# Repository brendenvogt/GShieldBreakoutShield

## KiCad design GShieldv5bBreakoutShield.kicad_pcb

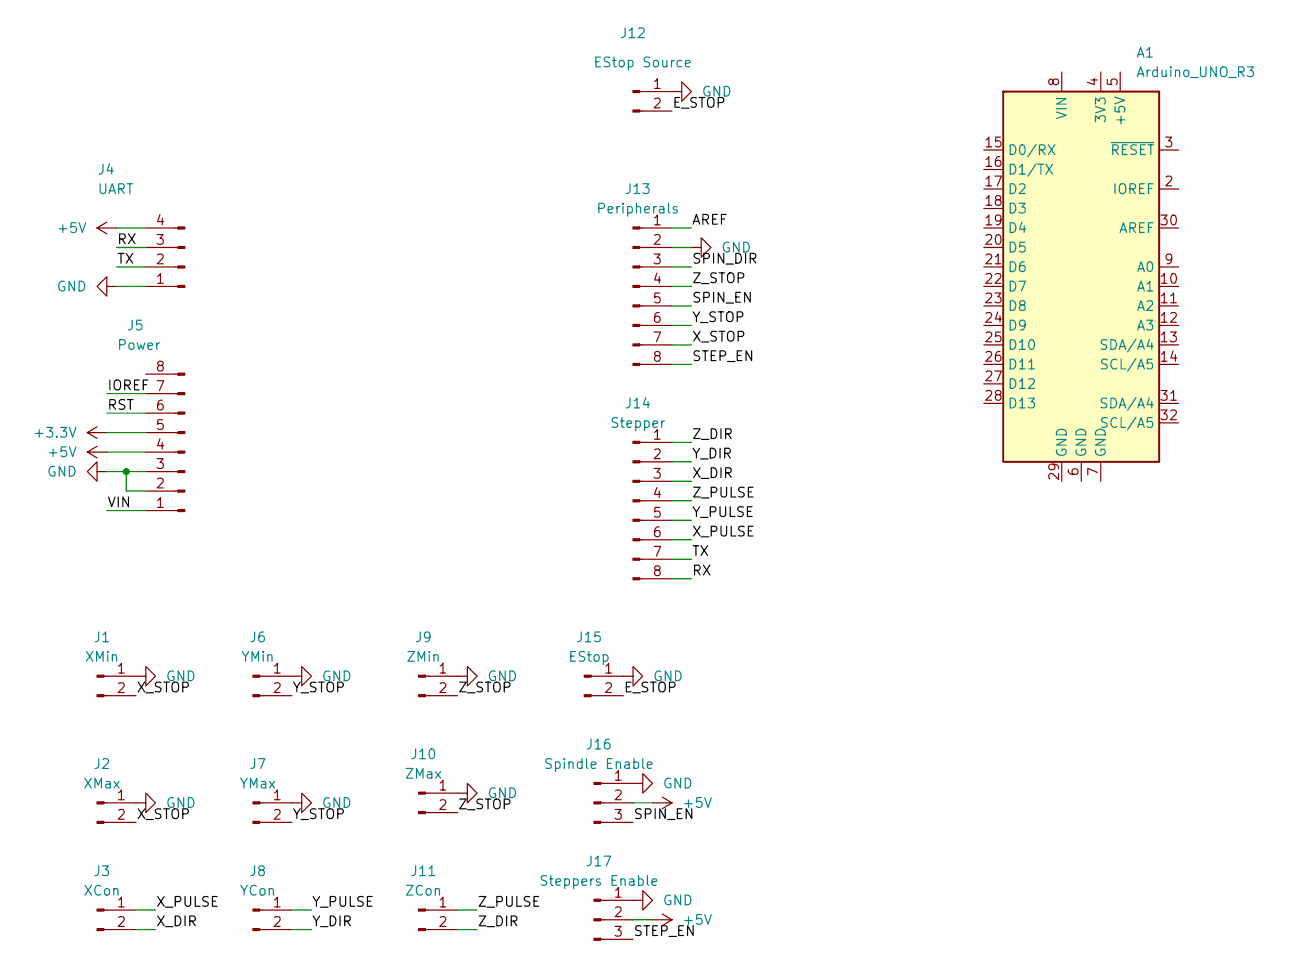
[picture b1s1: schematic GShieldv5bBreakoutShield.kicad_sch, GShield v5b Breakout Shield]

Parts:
A1: Arduino_UNO_R3
J1: XMin; PinHeader_1x02_P2.54mm_Vertical
J2: XMax; PinHeader_1x02_P2.54mm_Vertical
J3: XCon; PinHeader_1x02_P2.54mm_Vertical
J4: UART; PinHeader_1x04_P2.54mm_Vertical
J5: Power; PinHeader_1x08_P2.54mm_Vertical
J6: YMin; PinHeader_1x02_P2.54mm_Vertical
J7: YMax; PinHeader_1x02_P2.54mm_Vertical
J8: YCon; PinHeader_1x02_P2.54mm_Vertical
J9: ZMin; PinHeader_1x02_P2.54mm_Vertical
J10: ZMax; PinHeader_1x02_P2.54mm_Vertical
J11: ZCon; PinHeader_1x02_P2.54mm_Vertical
J12: EStop Source; PinHeader_1x02_P2.54mm_Vertical
J13: Peripherals; PinHeader_1x08_P2.54mm_Vertical
J14: Stepper; PinHeader_1x08_P2.54mm_Vertical
J15: EStop; PinHeader_1x02_P2.54mm_Vertical
J16: Spindle Enable; PinHeader_1x03_P2.54mm_Vertical
J17: Steppers Enable; PinHeader_1x03_P2.54mm_Vertical

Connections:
+3V3: J5.5
+5V: J4.4, J5.4, J16.2, J17.2
/AREF: J13.1
/E_STOP: J12.2, J15.2
/IOREF: J5.7
/RST: J5.6
/RX: J4.3, J14.8
/SPIN_DIR: J13.3
/SPIN_EN: J13.5, J16.3
/STEP_EN: J13.8, J17.3
/TX: J4.2, J14.7
/VIN: J5.1
/X_DIR: J3.2, J14.3
/X_PULSE: J3.1, J14.6
/X_STOP: J1.2, J2.2, J13.7
/Y_DIR: J8.2, J14.2
/Y_PULSE: J8.1, J14.5
/Y_STOP: J6.2, J7.2, J13.6
/Z_DIR: J11.2, J14.1
/Z_PULSE: J11.1, J14.4
/Z_STOP: J9.2, J10.2, J13.4
GND: J1.1, J2.1, J4.1, J5.2, J5.3, J6.1, J7.1, J9.1, J10.1, J12.1, J13.2, J15.1, J16.1, J17.1

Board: 2 copper layers, 18 parts (0 on the bottom side), 16 nets, no tracks yet.

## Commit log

2022-06-26 Added Kicad project
2022-06-26 Added preliminary shematic and layout without traces or vias

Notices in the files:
GShieldv5bBreakoutShield.kicad_sch:
License: GNU General Public License v3.0
